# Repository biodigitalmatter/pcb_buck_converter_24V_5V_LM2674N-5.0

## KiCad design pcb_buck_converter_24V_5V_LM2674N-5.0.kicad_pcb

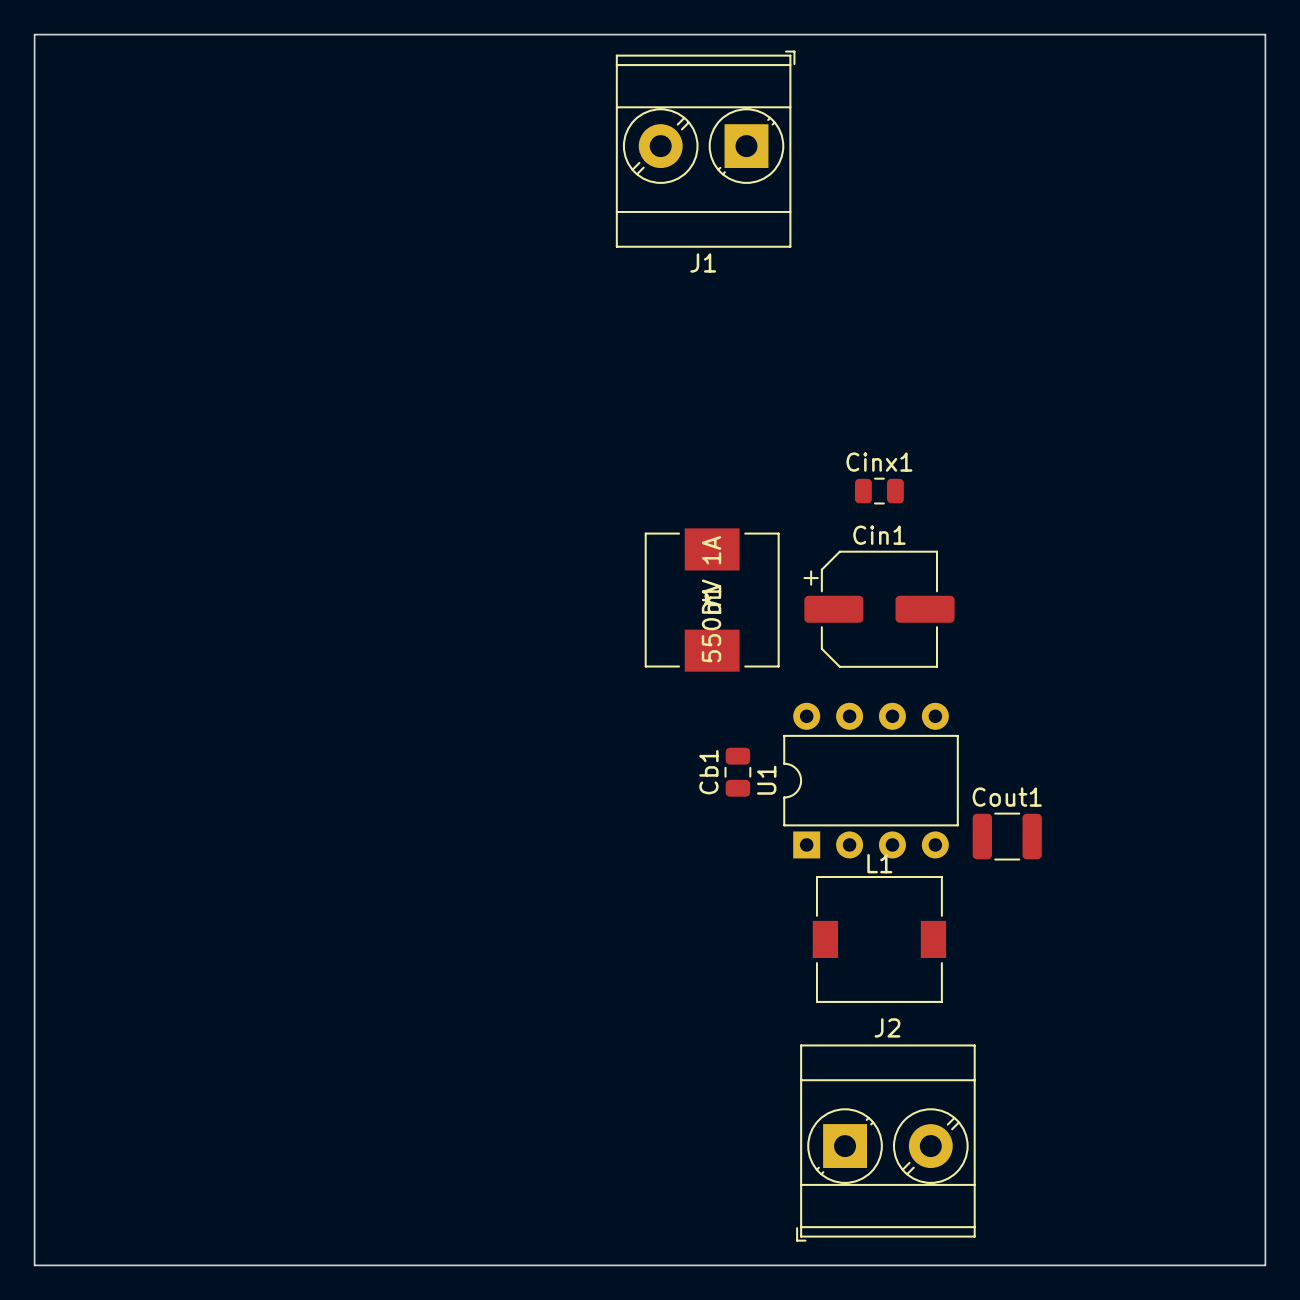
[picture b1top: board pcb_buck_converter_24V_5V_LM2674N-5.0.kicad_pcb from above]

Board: 2 copper layers, 72.9 x 72.9 mm, 9 parts (0 on the bottom side), 5 nets, no tracks yet.

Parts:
Cb1: 10 nF 0Ohm; C_0805_2012Metric
Cin1: 68uF 340mOhm; CP_Elec_6.3x7.7
Cinx1: 100nF 64mOhm; C_0805_2012Metric
Cout1: 47uF 3.037mOhm; C_1210_3225Metric
D1: 550mV 1A; DR74-151-R
J1, J2: Screw_Terminal_01x02; TerminalBlock_Phoenix_MKDS-3-2-5.08_1x02_P5.08mm_Horizontal
L1: 150uH 591mOhm; L_7.3x7.3_H3.5
U1: LM2674N-5; DIP-8_W7.62mm

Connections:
+5V: Cout1.1, J2.2, L1.2, U1.4 (FB)
+24V: Cin1.1, Cinx1.1, J1.2, U1.5 (ON/~OFF), U1.7 (VIN)
GNDPWR: Cin1.2, Cinx1.2, Cout1.2, D1.2 (A), J1.1, J2.1, U1.6 (GND)
unnamed: Cb1.1, U1.1 (CB)
unnamed: Cb1.2, D1.1 (K), L1.1, U1.8 (VSW)

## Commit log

2023-04-06 broken out from digital 24V to 5V breakout repo

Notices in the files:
parts and their libraries:
Copyright 2021 Accelerated Designs. All rights reserved.
